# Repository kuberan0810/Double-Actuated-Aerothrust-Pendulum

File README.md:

# Double-Actuated-Aerothrust-Pendulum
A double actuated aerothrust pendulum is a normal pendulum which is pivoted at one end and a Motor-propeller unit is attached to the other end and is allowed to swing freely. By controlling the trust produced by the motor-propeller unit, angle of the pendulum is controlled precisely
Video Link: https://www.youtube.com/watch?v=djl4IUnqU20

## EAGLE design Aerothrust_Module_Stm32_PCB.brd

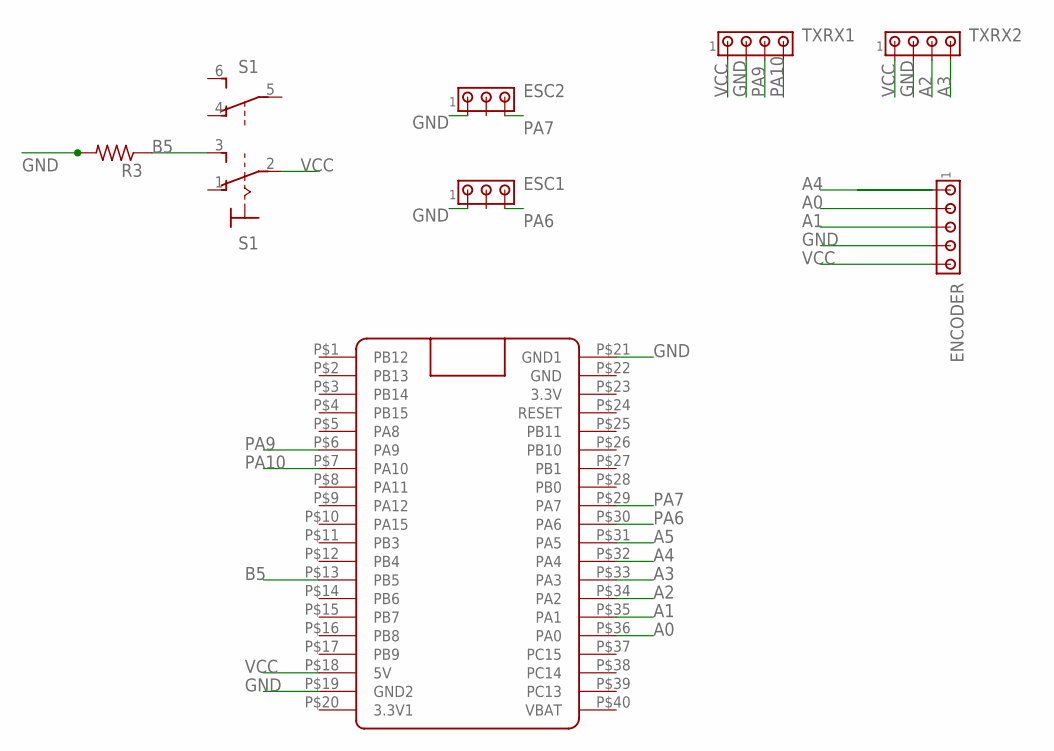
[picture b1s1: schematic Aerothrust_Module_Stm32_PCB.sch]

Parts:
ENCODER: MTA05-100; 10X05MTA
ESC1, ESC2: MTA03-100; 10X03MTA
R3: R-US_0207/10; 0207/10
S1: 320-938
TXRX1, TXRX2: MTA04-100; 10X04MTA
U$1: BLUE_PILL

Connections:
A0: ENCODER.2, U$1.P$36 (PA0)
A1: ENCODER.3, U$1.P$35 (PA1)
A2: TXRX2.3, U$1.P$34 (PA2)
A3: TXRX2.4, U$1.P$33 (PA3)
A4: ENCODER.1, U$1.P$32 (PA4)
A5: U$1.P$31 (PA5)
B5: R3.1, S1.3 (S), U$1.P$13 (PB5)
GND: ENCODER.4, ESC1.1, ESC2.1, R3.2, TXRX1.2, TXRX2.2, U$1.P$19 (GND2), U$1.P$21 (GND1)
PA6: ESC1.3, U$1.P$30 (PA6)
PA7: ESC2.3, U$1.P$29 (PA7)
PA9: TXRX1.3, U$1.P$6 (PA9)
PA10: TXRX1.4, U$1.P$7 (PA10)
VCC: ENCODER.5, S1.2, TXRX1.1, TXRX2.1, U$1.P$18 (5V)

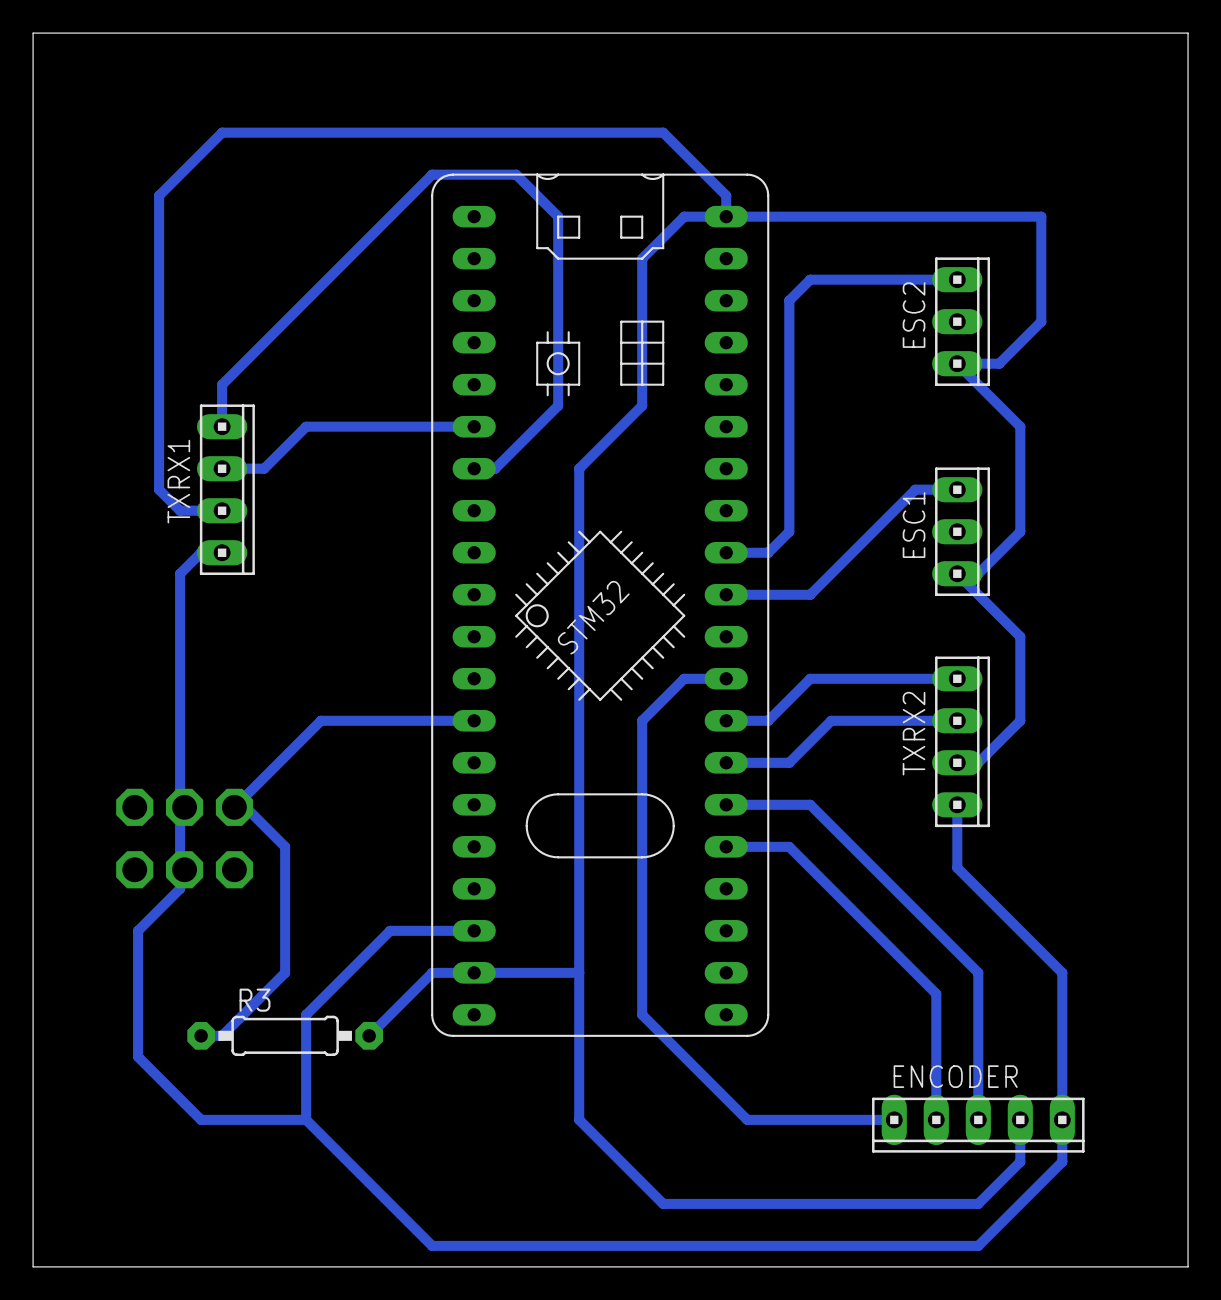
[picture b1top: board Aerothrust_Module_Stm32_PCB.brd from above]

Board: 2 copper layers, 69.8 x 74.6 mm, 8 parts (1 on the bottom side), 12 nets.

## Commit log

2021-06-27 Create curve_equation.py
    This python file will use linear regression model (polynomial regression) to calculate the damping co-efficient of the pendulum from free oscillation curve
